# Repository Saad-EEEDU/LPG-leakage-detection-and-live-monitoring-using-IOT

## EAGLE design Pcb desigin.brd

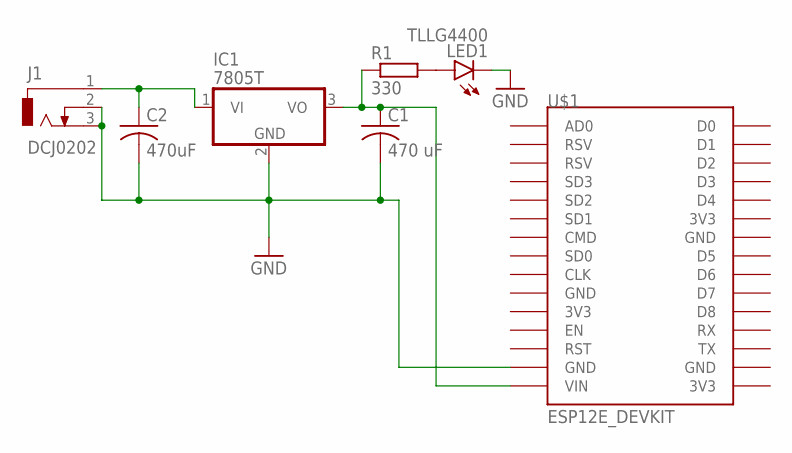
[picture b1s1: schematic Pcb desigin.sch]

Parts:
C1: 470 uF; C025-025X050
C2: 470uF; C025-025X050
IC1: 7805T; TO220H
J1: DCJ0202
LED1: TLLG4400; LED3MM
R1: 330; RDH/15
U$1: ESP12E_DEVKIT

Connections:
GND: C1.2, C2.2, IC1.2 (GND), J1.2, J1.3, LED1.K (C), U$1.GND@1 (GND)
unnamed: LED1.A, R1.2
unnamed: C2.1, IC1.1 (VI), J1.1
unnamed: C1.1, IC1.3 (VO), R1.1, U$1.VIN

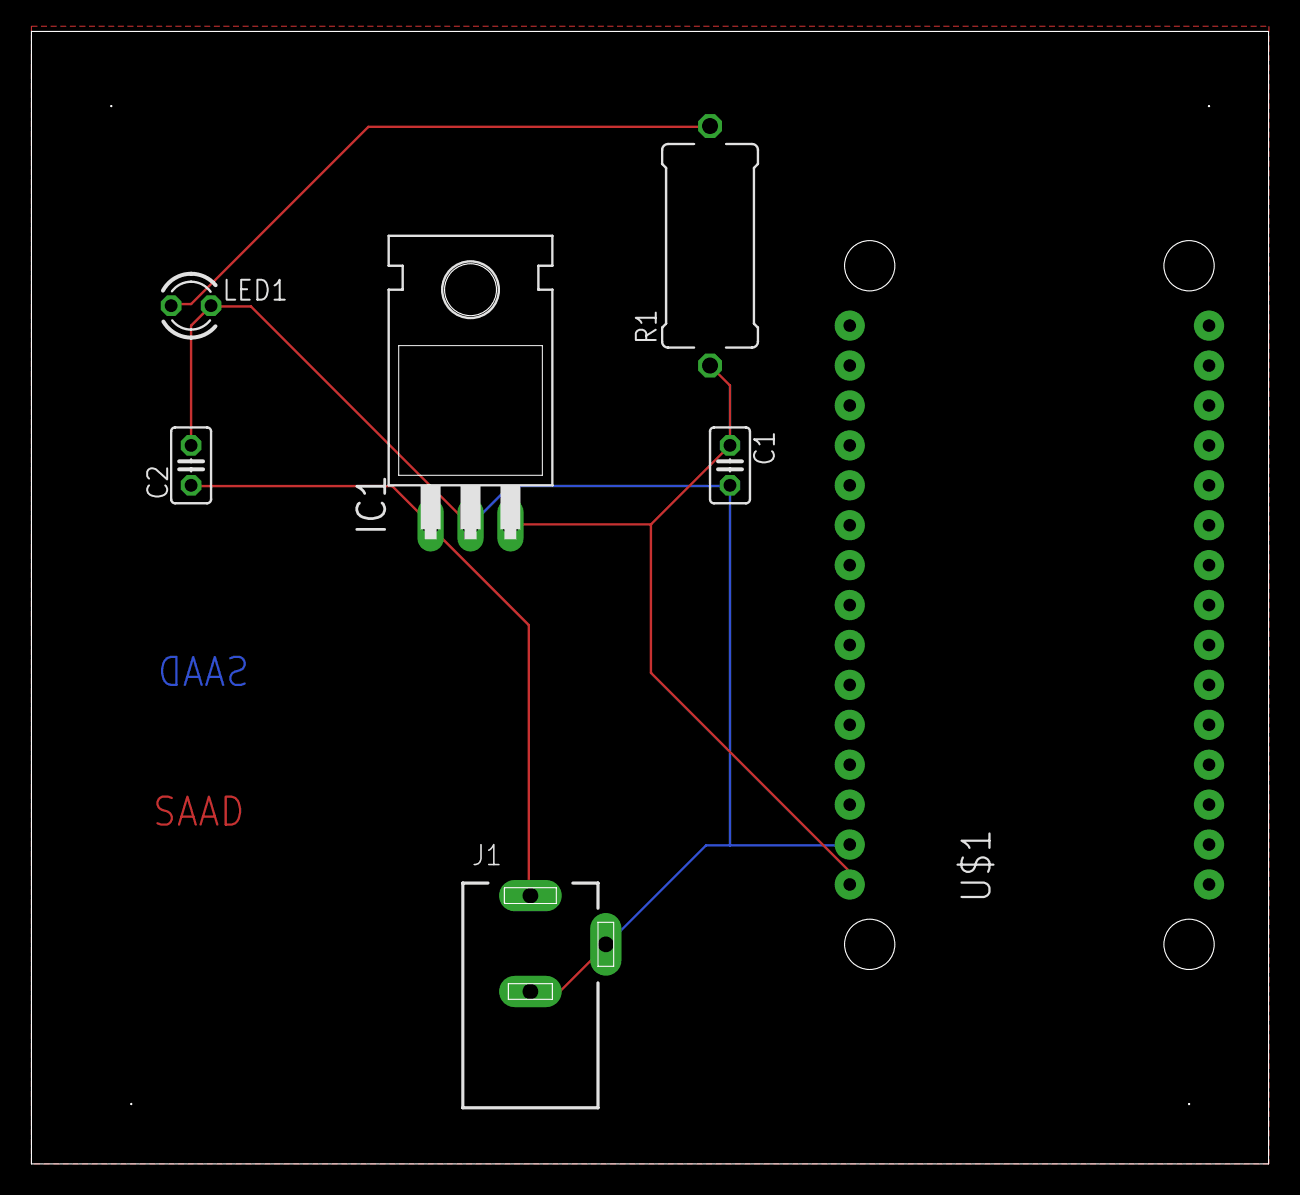
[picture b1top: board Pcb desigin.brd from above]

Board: 2 copper layers, 78.7 x 72.1 mm, 7 parts (0 on the bottom side), 4 nets.
